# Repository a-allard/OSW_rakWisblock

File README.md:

# OSW_rakWisblock

This project is a smart watch with the same outline as [watchy](https://github.com/sqfmi/watchy-hardware).  This uses a generic footprint that should work with any of the [RAK wisblock](https://docs.rakwireless.com/Product-Categories/WisDuo/) cores.  

### Supporting future development
If you like this project, please consider supporting my open source projects through:  (Note if you use the pcbway link below to order the project it does not cost you anymore but it does help me)
* 
*

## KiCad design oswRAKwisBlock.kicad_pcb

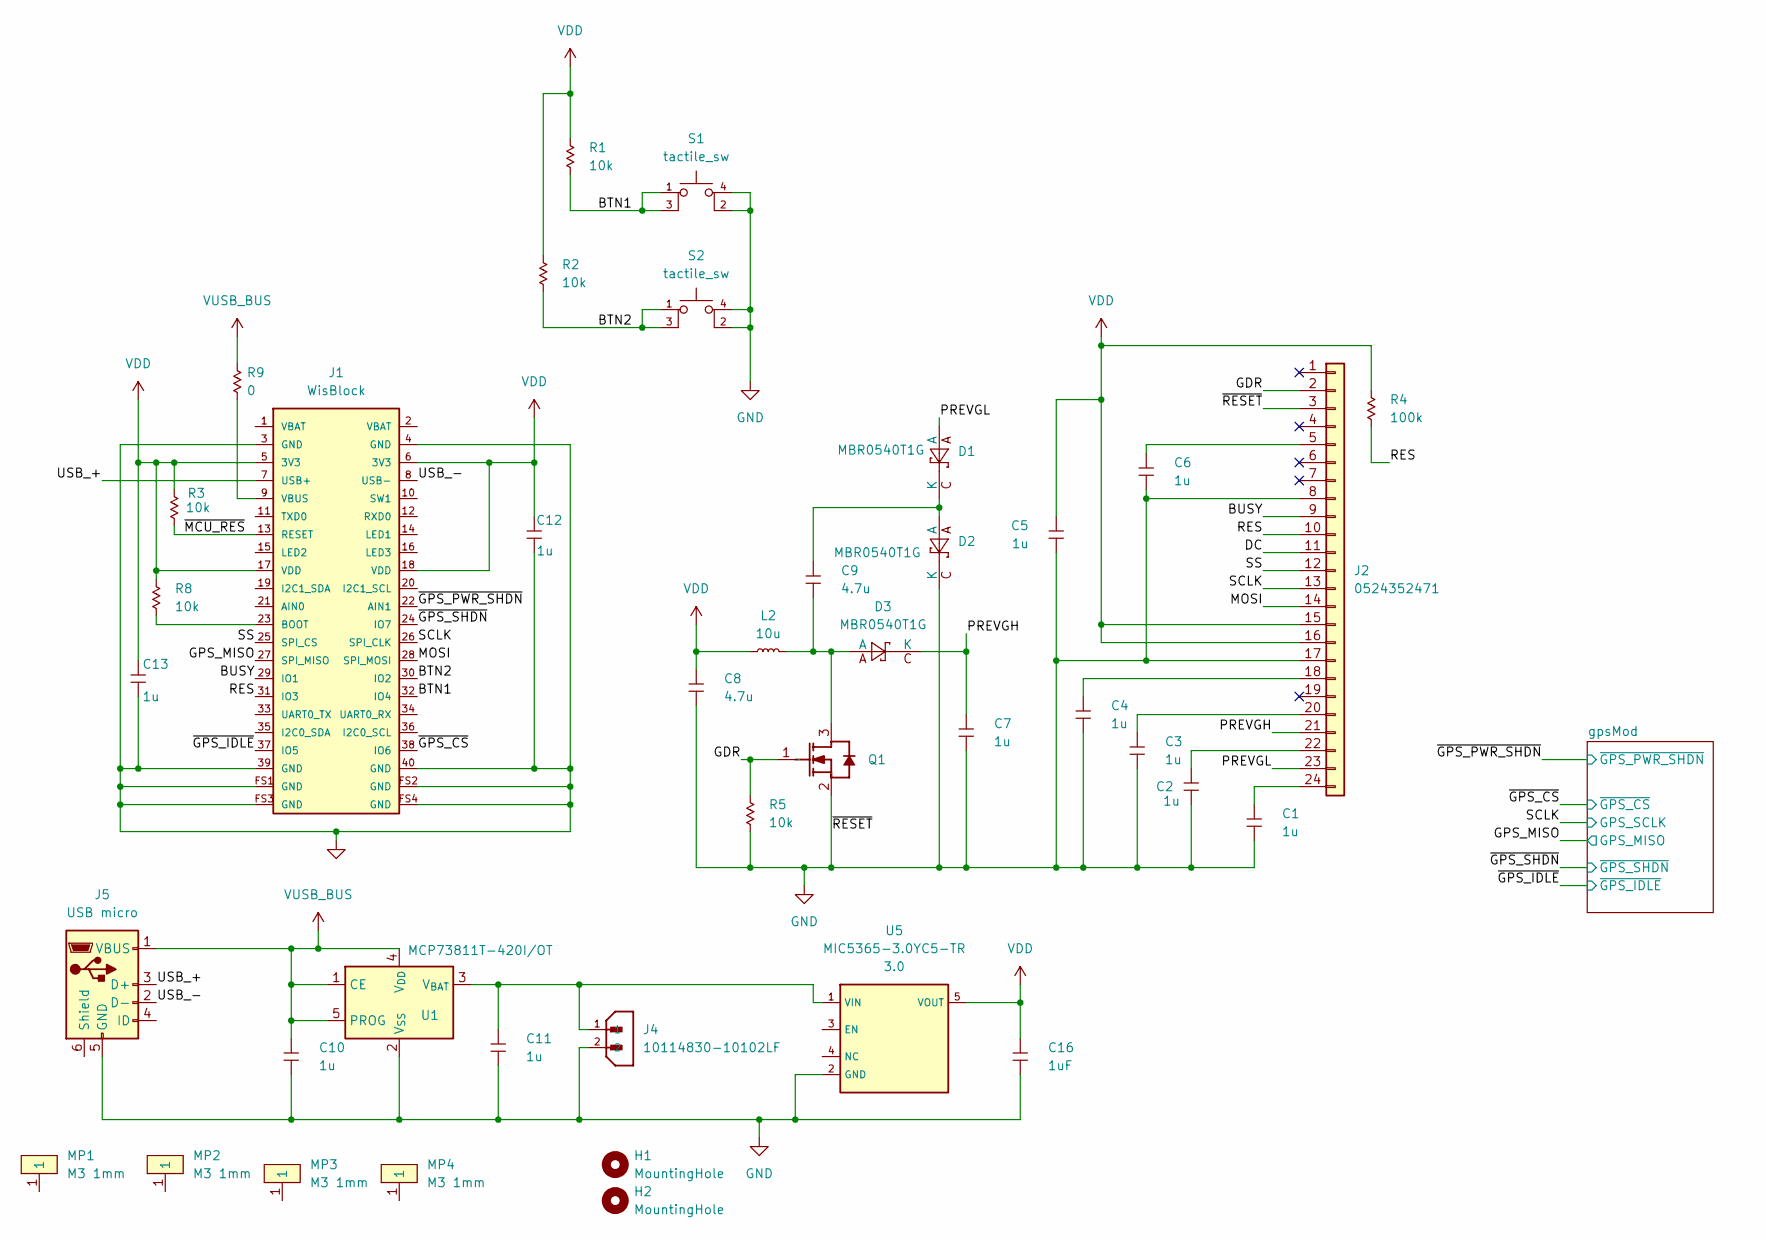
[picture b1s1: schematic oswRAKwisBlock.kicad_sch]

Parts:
C1, C2, C3, C4, C5, C6, C7: 1u; CAPC100X50X60L25N; Voltage 50V; Tolerance 20%; MPN GRM155R61H105ME05D
C8, C9: 4.7u; CAPC200X125X145L45N; Voltage 50V; Tolerance 20%; MPN GRM21BZ71H475ME15K
C10, C11, C12, C13: 1u; CAPC100X50X60L25N; Voltage 10V; Tolerance 10%; MPN GRM155Z71A105KE01J
C16: 1uF; CAPC60X30X39L17N; Voltage 6.3V; Tolerance 10%; MPN GRM033D70J105ME01D
D1, D2, D3: MBR0540T1G; SOD370X155X135L32X57L; Voltage 80V; MPN MBR0580S1-7
H1, H2: MountingHole; MountingHole_2.2mm_M2
J1: WisBlock; TXGA_FBB04004-F40S1003K6M; MPN FBB04004-F40S1003K6M
J2: 0524352471; MOLEX_52435-2471; MPN 0524352471
J4: 10114830-10102LF; AMPHENOL_10114830-10102LF; MPN 10114830-10102LF
J5: USB micro; GCT_USB3075-30-A; MPN USB3075-30-A
L2: 10u; INDC400X400X120L120N; Tolerance 20%; MPN SRN4012BTA-100M
MP1, MP2, MP3, MP4: M3 1mm; MTGNP300H213Z565
Q1: SI1308EDL-T1-GE3; SOT23-3P65_210X110L20X32L; Voltage 30V; MPN SI1308EDL-T1-GE3
R1, R2, R3, R5, R8: 10k; RESC40X20X15L10N; Tolerance 1%; MPN ERJ-XGNF1002Y
R4: 100k; RESC40X20X15L10N; Tolerance 1%; MPN ERJ-XGNF1003Y
R9: 0; RESC60X30X26L15N; Tolerance 1%; MPN ERJ-1GN0R00C
S1, S2: tactile_sw; Panasonic_EVQPUA02K; MPN EVQ-PUA02K
U1: MCP73811T-420I/OT; SOT23-5P95_270X145L35X35L; Voltage 3.75-6; MPN MCP73811T-420I/OT
U5: MIC5365-3.0YC5-TR; SOT23-5P65_210X110L33X22N; Voltage 3.0; MPN MIC5365-3.0YC5-TR

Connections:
/BTN1: J1.32 (IO4), R1.2, S1.1, S1.3 (K)
/BTN2: J1.30 (IO2), R2.2, S2.1, S2.3 (K)
/BUSY: J1.29 (IO1), J2.9
/DC: J2.11
/GDR: J2.2, Q1.1 (G), R5.1
/GPS_MISO: J1.27 (SPI_MISO); also elsewhere on the board
/MOSI: J1.28 (SPI_MOSI), J2.14
/PREVGH: C7.1, D3.C (K), J2.21
/PREVGL: D1.A, J2.23
/RES: J1.31 (IO3), J2.10, R4.2
/SCLK: J1.26 (SPI_CLK), J2.13; also elsewhere on the board
/SS: J1.25 (SPI_CS), J2.12
/USB_+: J1.7 (USB+), J5.3 (D+)
/USB_-: J1.8 (USB-), J5.2 (D-)
/~GPS_CS: J1.38 (IO6); also elsewhere on the board
/~GPS_IDLE: J1.37 (IO5); also elsewhere on the board
/~GPS_PWR_SHDN: J1.22 (AIN1); also elsewhere on the board
/~GPS_SHDN: J1.24 (IO7); also elsewhere on the board
/~MCU_RES: J1.13 (RESET), R3.2
GND: C1.2, C2.2, C3.2, C4.2, C5.2, C6.2, C7.2, C8.2, C10.2, C11.2, C12.2, C13.2, C16.2, D2.C (K), J1.3 (GND), J1.4 (GND), J1.39 (GND), J1.40 (GND), J1.FS1 (GND), J1.FS2 (GND), J1.FS3 (GND), J1.FS4 (GND), J2.3, J2.8, J2.17, J4.2, J5.5 (GND), Q1.2 (S), R5.2, S1.2, S1.4 (A), S2.2, S2.4 (A), U1.2 (V_{SS}), U5.2 (GND); also elsewhere on the board
unnamed: C9.1, D1.C (K), D2.A
unnamed: J1.23 (BOOT), R8.2
unnamed: J1.9 (VBUS), R9.2
unnamed: C6.1, J2.5
unnamed: C4.1, J2.18
unnamed: C3.1, J2.20
unnamed: C2.1, J2.22
unnamed: C1.1, J2.24
unnamed: C9.2, D3.A, L2.2, Q1.3 (D)
unnamed: C11.1, J4.1, U1.3 (V_{BAT}), U5.1 (VIN)
VDD: C5.1, C8.1, C12.1, C13.1, C16.1, J1.5 (3V3), J1.6 (3V3), J1.17 (VDD), J1.18 (VDD), J2.15, J2.16, L2.1, R1.1, R2.1, R3.1, R4.1, R8.1, U5.5 (VOUT); also elsewhere on the board
VUSB_BUS: C10.1, J5.1 (VBUS), R9.1, U1.1 (CE), U1.4 (V_{DD}), U1.5 (PROG)

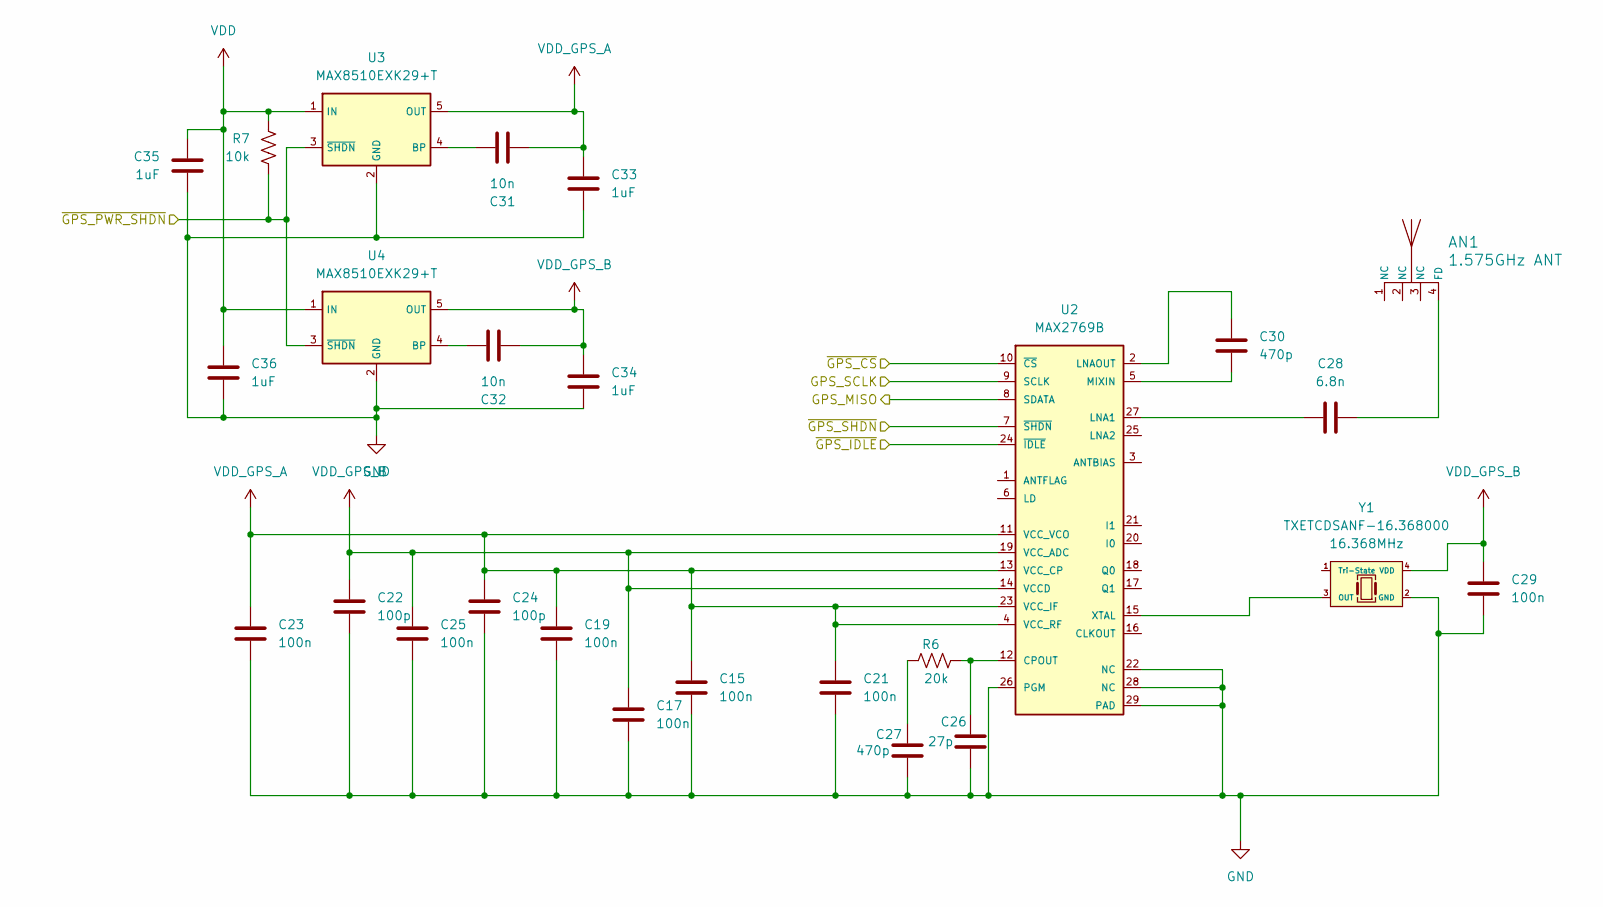
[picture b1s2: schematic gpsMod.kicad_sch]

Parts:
AN1: 1.575GHz ANT; MOLEX_1462350001_CHIP; MPN 1462350001
C15, C17, C19, C21, C23, C25, C29: 100n; CAPC60X30X39L17L; Voltage 16V; Tolerance 10%; MPN GRM033Z71C104KE14D
C22, C24: 100p; CAPC60X30X33L15L; Voltage 50V; Tolerance 10%; MPN GRM033R71H101KA12D
C26: 27p; CAPC60X30X33L15L; Voltage 25V; Tolerance 5%; MPN GRM0335C1E270JA01D
C27, C30: 470p; CAPC60X30X33L15L; Voltage 50V; Tolerance 10%; MPN GRM033R71H471KA12D
C28: 6.8n; CAPC60X30X33L15L; Voltage 25V; Tolerance 10%; MPN GRM033R71E682KE14D
C31, C32: 10n; CAPC40X20X22L10L; Voltage 50V; Tolerance 10%; MPN GRM022C71A103KE01L
C33, C34, C35, C36: 1uF; CAPC60X30X39L17L; Voltage 6.3V; Tolerance 10%; MPN GRM033D70J105ME01D
R6: 20k; RESC60X30X26L15L; Tolerance 1%; MPN ERJ-1GNF2002C
R7: 10k; RESC40X20X15L10L; Tolerance 1%; MPN ERJ-XGNF1002Y
U2: MAX2769B; QFN29P50_500X500X80L55X25T325L; MPN MAX2769BETI/V+T
U3, U4: MAX8510EXK29+T; SOT23-5P65_210X110L42X22L; Voltage 2.85V; MPN MAX8510EXK29+T
Y1: TXETCDSANF-16.368000; OSCDFN4_250X320X100L70X80L; Tolerance 2ppm; MPN TXETCDSANF-16.368000

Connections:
/GPS_MISO: U2.8 (SDATA); also elsewhere on the board
/SCLK: U2.9 (SCLK); also elsewhere on the board
/~GPS_CS: U2.10 (~CS); also elsewhere on the board
/~GPS_IDLE: U2.24 (~IDLE); also elsewhere on the board
/~GPS_PWR_SHDN: R7.2, U3.3 (~SHDN), U4.3 (~SHDN); also elsewhere on the board
/~GPS_SHDN: U2.7 (~SHDN); also elsewhere on the board
GND: C15.2, C17.2, C19.2, C21.2, C22.2, C23.2, C24.2, C25.2, C26.2, C27.2, C29.2, C33.2, C34.2, C35.2, C36.2, U2.22 (NC), U2.26 (PGM), U2.28 (NC), U2.29 (PAD), U3.2 (GND), U4.2 (GND), Y1.2 (GND); also elsewhere on the board
unnamed: AN1.4 (FD), C28.2
unnamed: C27.1, R6.1
unnamed: C26.1, R6.2, U2.12 (CPOUT)
unnamed: C28.1, U2.27 (LNA1)
unnamed: C30.1, U2.2 (LNAOUT)
unnamed: C30.2, U2.5 (MIXIN)
unnamed: U2.15 (XTAL), Y1.3 (OUT)
unnamed: C31.1, U3.4 (BP)
unnamed: C32.1, U4.4 (BP)
VDD: C35.1, C36.1, R7.1, U3.1 (IN), U4.1 (IN); also elsewhere on the board
VDD_GPS_A: C15.1, C19.1, C21.1, C23.1, C24.1, C31.2, C33.1, U2.4 (VCC_RF), U2.11 (VCC_VCO), U2.13 (VCC_CP), U2.23 (VCC_IF), U3.5 (OUT); also elsewhere on the board
VDD_GPS_B: C17.1, C22.1, C25.1, C29.1, C32.2, C34.1, U2.14 (VCCD), U2.19 (VCC_ADC), U4.5 (OUT), Y1.4 (VDD); also elsewhere on the board

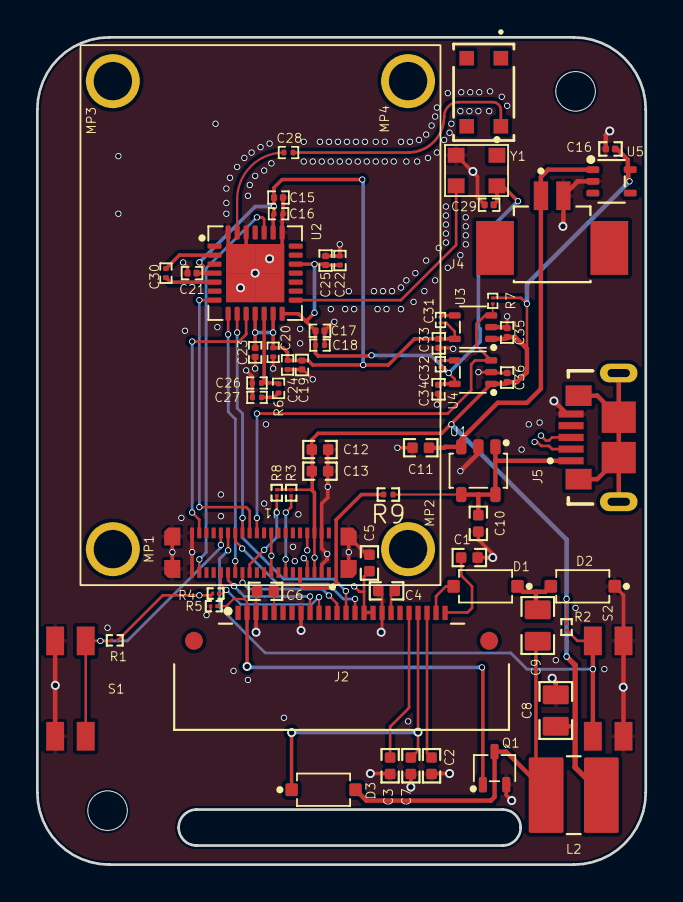
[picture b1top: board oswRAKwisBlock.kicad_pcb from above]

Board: 4 copper layers, 33.8 x 46.0 mm, 69 parts (0 on the bottom side), 42 nets.

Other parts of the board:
C16#2, C18, C20: 100p; CAPC60X30X33L15L

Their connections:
GND: C16#2.2, C18.2, C20.2; also elsewhere on the board
VDD_GPS_A: C16#2.1, C20.1; also elsewhere on the board
VDD_GPS_B: C18.1; also elsewhere on the board

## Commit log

2024-02-03 Adding the generic git files.
2024-02-03 kicad project start....
2024-02-03 Adding watchy outline.
2024-02-05 Adding connector.
2024-02-09 Getting the wisblock footprint on the board.
2024-02-11 Fixing the mounting hole issue.
2024-02-15 Adding the FPs to the board.
2024-02-16 Updates.
2024-02-16 Working forward.
2024-02-24 Updating the board and moving some things around.
2024-02-25 Working on it....
2024-02-25 Working on getting the placement settled. VERY TIGHTgit pull!
2024-02-26 Adding a bunch of stuff to the design and some local models.
2024-02-27 Working on the board a bit more.
2024-03-13 Working on things.
2024-03-18 Finally got the GPS chip wired in. Just need to finish the pinout and then finalize the GPS part placement.
2024-03-18 Made the RAK module semi transparent so I can layout the stuff underneath and check for collisions.
2024-03-19 Finished schematic. Time to layout.
2024-03-20 Working on the layout a bit. Need confirmation on the USB port before I go much further.
2024-03-22 Moving parts around to start layout.
2024-03-23 starting to lay the board out.
2024-03-25 Moving some stuff around.
2024-03-25 Mirroring layout to match watchy layout better.
2024-03-26 Adding mounting holes.
2024-03-30 working on the layout some.
2024-03-31 Forgot to put the VBUS connection to the RAK mod. Done now.
2024-03-31 Working on connect the dots.....
2024-04-01 playing with layout as it is very tight.
2024-04-06 Finishing up the layout.
2024-04-06 a couple minor tweaks to the layout (better trace connections) and moving a hole to be in the proper location
2024-04-06 Adding the html BOM and updating the pdf schematic (now moved to a correctly named folder.
2024-04-06 updates to the project file.
2024-04-06 documentation update.
2024-04-06 Added production files
